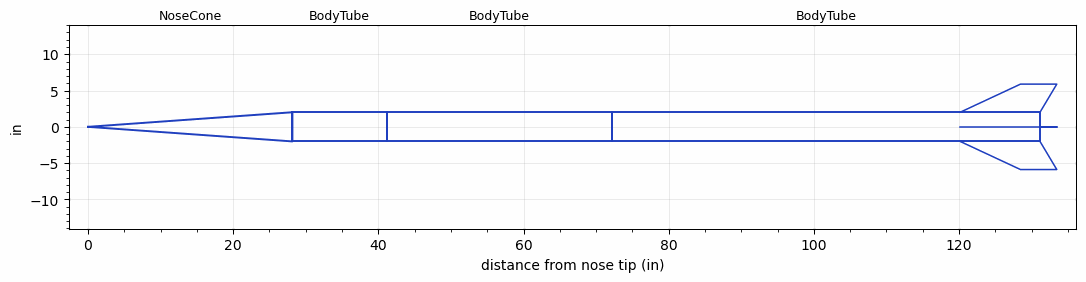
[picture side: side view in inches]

<RASAeroDocument>
 <FileVersion>2</FileVersion>
 <RocketDesign>
  <NoseCone>
   <Length>28.16</Length>
   <Diameter>4.02</Diameter>
   <Shape>Conical</Shape>
   <Location>0</Location>
  </NoseCone>
  <BodyTube>
   <Length>13</Length>
   <Diameter>4.02</Diameter>
   <Location>28.16</Location>
  </BodyTube>
  <BodyTube>
   <Length>31</Length>
   <Diameter>4.02</Diameter>
   <Location>41.16</Location>
  </BodyTube>
  <BodyTube>
   <Length>59</Length>
   <Diameter>4.02</Diameter>
   <RailGuideDiameter>0.5</RailGuideDiameter>
   <RailGuideHeight>0.5</RailGuideHeight>
   <Location>72.16</Location>
   <Fin>
    <Count>4</Count>
    <Chord>11</Chord>
    <Span>3.875</Span>
    <SweepDistance>8.31</SweepDistance>
    <TipChord>5</TipChord>
    <Thickness>0.4</Thickness>
    <Location>11</Location>
    <AirfoilSection>Hexagonal</AirfoilSection>
    <FX1>0.7</FX1>
    <FX3>0.7</FX3>
   </Fin>
   <Protuberance>
    <StreamlinedNoBaseDrag>0</StreamlinedNoBaseDrag>
    <StreamlinedWithBaseDrag>3</StreamlinedWithBaseDrag>
    <InclinedPlate1Angle>0</InclinedPlate1Angle>
    <InclinedPlate1FrontalArea>0</InclinedPlate1FrontalArea>
    <InclinedPlate2Angle>0</InclinedPlate2Angle>
    <InclinedPlate2FrontalArea>0</InclinedPlate2FrontalArea>
   </Protuberance>
  </BodyTube>
  <Surface>Polished</Surface>
  <ModifiedBarrowman>False</ModifiedBarrowman>
  <Turbulence>False</Turbulence>
  <SustainerNozzle>3</SustainerNozzle>
  <UseBooster1>False</UseBooster1>
  <UseBooster2>False</UseBooster2>
 </RocketDesign>
 <LaunchSite>
  <Altitude>4250</Altitude>
  <Pressure>0</Pressure>
  <RodAngle>6</RodAngle>
  <RodLength>17</RodLength>
  <Temperature>75</Temperature>
  <WindSpeed>0</WindSpeed>
 </LaunchSite>
 <Recovery>
  <Altitude1>1000</Altitude1>
  <Altitude2>1000</Altitude2>
  <DeviceType1>None</DeviceType1>
  <DeviceType2>None</DeviceType2>
  <Event1>False</Event1>
  <Event2>False</Event2>
  <Size1>1</Size1>
  <Size2>1</Size2>
  <EventType1>None</EventType1>
  <EventType2>None</EventType2>
  <CD1>1.33</CD1>
  <CD2>1.33</CD2>
 </Recovery>
 <SimulationList>
  <Simulation>
   <SustainerEngine>N2540-GR-P  (CTI)</SustainerEngine>
   <SustainerLaunchWt>66.5</SustainerLaunchWt>
   <SustainerNozzleDiameter>3</SustainerNozzleDiameter>
   <SustainerCG>91.72</SustainerCG>
   <SustainerIgnitionDelay>0</SustainerIgnitionDelay>
   <Booster1SeparationDelay>0</Booster1SeparationDelay>
   <Booster1IgnitionDelay>0</Booster1IgnitionDelay>
   <IncludeBooster1>False</IncludeBooster1>
   <Booster2Delay>0</Booster2Delay>
   <IncludeBooster2>False</IncludeBooster2>
   <TimetoApogee>42.12894</TimetoApogee>
   <MaxAltitude>31416.33</MaxAltitude>
   <MaxVelocity>1925.781</MaxVelocity>
   <OptimumWt>36.62868</OptimumWt>
   <OptimumMaxAlt>36.62868</OptimumMaxAlt>
  </Simulation>
 </SimulationList>
</RASAeroDocument>
